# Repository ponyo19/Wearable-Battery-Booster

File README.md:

# Wearable-Battery-Booster
Wearable Battery Booster Project for the 2024 Protocamp course at Aalto University

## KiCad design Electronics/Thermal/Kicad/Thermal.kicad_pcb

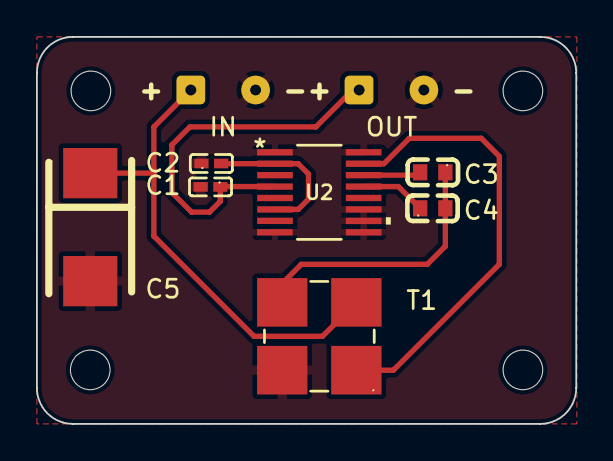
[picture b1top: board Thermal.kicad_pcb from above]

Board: 2 copper layers, 30.0 x 21.5 mm, 9 parts (0 on the bottom side), 8 nets.

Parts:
C1: 10u; C0402
C2: 1u; C0402
C3: 4.7n; C0603
C4: 330p; C0603
C5: 220u; CASE-D_7343
IN: Energy Generator Connection; SolderWire-0.1sqmm_1x02_P3.6mm_D0.4mm_OD1mm
OUT: Output; SolderWire-0.1sqmm_1x02_P3.6mm_D0.4mm_OD1mm
T1: 1:50; XFMR-SMD_LPR6235-752SML
U2: LTC3108IGN_PBF; SSOP-16_GW

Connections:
C1: C3.1, U2.13 (C1)
C2: C4.2, U2.14 (C2)
DC+: C5.1, IN.1, T1.2 (AB)
DC-: C1.2, C2.1, C5.2, IN.2, OUT.2, T1.4 (SB), U2.1 (GND_2), U2.8 (GND_3), U2.9 (GND_4), U2.10 (VS2), U2.11 (VS1), U2.16 (GND)
unnamed: C2.2, U2.2 (VAUX), U2.6 (VLDO)
unnamed: C3.2, C4.1, T1.3 (SA)
SW: T1.1 (AA), U2.15 (SW)
Vout: C1.1, OUT.1, U2.4 (VOUT)

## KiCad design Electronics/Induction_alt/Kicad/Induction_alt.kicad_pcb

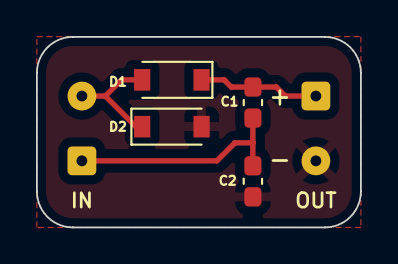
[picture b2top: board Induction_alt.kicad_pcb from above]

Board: 2 copper layers, 18.0 x 10.6 mm, 6 parts (0 on the bottom side), 4 nets.

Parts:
C1, C2: C_Polarized_Small_US; C_0603_1608Metric_Pad1.08x0.95mm_HandSolder
D1, D2: D_Schottky; D_SOD-123
IN: AC_IN; SolderWire-0.1sqmm_1x02_P3.6mm_D0.4mm_OD1mm
OUT: DC_OUT; SolderWire-0.1sqmm_1x02_P3.6mm_D0.4mm_OD1mm

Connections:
GND: C2.2, D2.2 (A), OUT.2
unnamed: C1.2, C2.1, IN.1
unnamed: D1.2 (A), D2.1 (K), IN.2
VOUT: C1.1, D1.1 (K), OUT.1

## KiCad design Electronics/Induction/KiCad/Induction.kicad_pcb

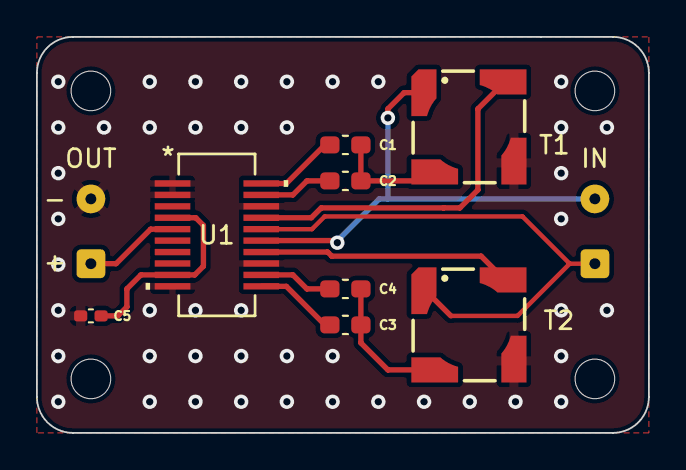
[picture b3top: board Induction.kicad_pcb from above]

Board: 2 copper layers, 34.0 x 22.0 mm, 10 parts (0 on the bottom side), 13 nets.

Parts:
C1, C3: 1n; C_0603_1608Metric_Pad1.08x0.95mm_HandSolder
C2, C4: 470p; C_0603_1608Metric_Pad1.08x0.95mm_HandSolder
C5: 1u; C_0402_1005Metric_Pad0.74x0.62mm_HandSolder
IN: AC Input Connector; SolderWire-0.1sqmm_1x02_P3.6mm_D0.4mm_OD1mm
OUT: DC Output Connector; SolderWire-0.1sqmm_1x02_P3.6mm_D0.4mm_OD1mm
T1, T2: 1:100; WE-EHPI_5838
U1: LTC3109EGN-PBF; SSOP-20_GN_LIT

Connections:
C1A: C1.2, U1.20 (C1A)
C1B: C3.2, U1.11 (C1B)
C2A: C2.2, U1.19 (C2A)
C2B: C4.2, U1.12 (C2B)
GND: C5.1, OUT.2, T1.3 (SA), T2.3 (SA), U1.1 (VS1), U1.2 (VS2), U1.10 (GND), U1.13 (GND), U1.18 (GND)
unnamed: C1.1, C2.1, T1.4 (SB)
unnamed: C3.1, C4.1, T2.4 (SB)
unnamed: C5.2, U1.4 (VAUX), U1.9 (VLDO)
SWA: T1.2 (AB), U1.17 (SWA)
SWB: T2.2 (AB), U1.14 (SWB)
VINA: IN.1, T2.1 (AA), U1.16 (VINA)
VINB: IN.2, T1.1 (AA), U1.15 (VINB)
VOUT: OUT.1, U1.5 (VOUT)

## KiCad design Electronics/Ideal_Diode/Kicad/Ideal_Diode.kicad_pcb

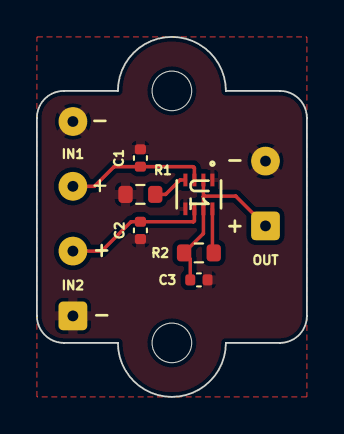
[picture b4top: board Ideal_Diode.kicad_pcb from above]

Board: 2 copper layers, 15.0 x 20.0 mm, 8 parts (0 on the bottom side), 6 nets.

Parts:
C1, C2: 1u; C_0402_1005Metric
C3: 0.1u; C_0402_1005Metric
IN: IN; SolderWire-0.1sqmm_1x04_P3.6mm_D0.4mm_OD1mm
OUT: OUT; SolderWire-0.1sqmm_1x02_P3.6mm_D0.4mm_OD1mm
R1, R2: 100k; R_0603_1608Metric
U1: LM66200DRLR; SOT-5X3_DRL_TEX

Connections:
GND: C1.1, C2.1, C3.2, IN.1, IN.4, OUT.2, R1.1, U1.1 (GND), U1.5 (GND)
unnamed: C3.1, OUT.1, R2.1, U1.2 (VOUT), U1.7 (VOUT)
unnamed: R1.2, U1.4 (ON)
unnamed: R2.2, U1.8 (ST)
VIN1: C1.2, IN.3, U1.3 (VIN1)
VIN2: C2.2, IN.2, U1.6 (VIN2)

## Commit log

2024-08-28 Add electronics
2024-08-28 Add readme files
2024-08-29 Add simulation and analyisis files
2024-08-30 Added drawings for rotational generator
2024-08-30 Add Final Report
2024-08-30 Update Final Report
